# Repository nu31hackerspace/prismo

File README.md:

# Prismo – a simple NFC access controller

| Demo | PCB |
| --- | --- |
|  |  |

Prismo is an open-source NFC access controller that you can build yourself for ~500 UAH (~10 USD).
Tap a card to unlock a door or power on a machine — fully self-hosted, MIT-licensed.

<!-- HERO IMAGE — replace with a clean, well-lit photo or render of the assembled device. -->
<!--  -->

<!-- DEMO GIF — ~5s: card tap → LED turns green → relay clicks / door opens. Autoplays in GitHub. -->
<!--  -->

You can use it, for example, to:

- Open a door
- Turn on a machine
- Control whatever you want with an NFC card/key

## Features

- 🟢 **Tap-to-unlock** — present an NFC/RFID card, get instant LED + buzzer feedback and a relay action.
- 🔓 **Build it yourself for ~$10** — off-the-shelf ESP32-C3 + PN532, single-layer PCB.
- 🛠️ **DIY-friendly PCB** — single-layer, etchable at home; a great first soldering project.
- 🏠 **Self-hosted + MQTT** — integrates with Home Assistant or your own backend. No cloud lock-in.
- ⚡ **One-click flashing** — flash a pre-built firmware from your browser, no toolchain required.

## How we test our solution

Every change **Tested on real hardware** — every change runs using a physical Prismo device.
We have a test stand that allows us to verify every change and make sure everything works as expected. For more info read the [ReadMe from blackbox-e2e](/blackbox-e2e/README.md).

## What you need

| Item | Notes |
| --- | --- |
| ESP32-C3 Super Mini | The brains. ~$3. |
| PN532 NFC module | Reads the cards (powered from 3.3 V). |
| Prismo PCB + components | See the [Bill of Materials](hardware/README.md#bom-file). |
| A USB-C cable + a Chrome/Edge browser | For flashing over Web Serial. |
| 2.4 GHz WiFi | The ESP32-C3 is 2.4 GHz only. |

## Quick start

> Full build instructions live in [`hardware/README.md`](hardware/README.md) (PCB + assembly)
> and [`firmware/README.md`](firmware/README.md) (firmware).

1. **Build the board** — etch/order the [single-layer PCB](hardware/README.md), solder the
   components, and connect the PN532 and RGB LED.
2. **Flash it** — open the web flasher in Chrome and click Flash. No toolchain needed.
3. **Connect it** — the device boots, joins your 2.4 GHz WiFi, and announces itself over MQTT.
4. **Add your card** — register the card's UID in the web app; tap to unlock.

## Why are we making Prismo?

We started Prismo because we could not find a simple, low‑cost project that:

- Uses easy hardware
- Uses simple, free software
- Is friendly for beginners

Before building more features, we wrote down what we want from this project.

### General requirements

- You do not need special knowledge to build and use Prismo.
- You do not need any paid software. Everything needed is free.

### Hardware requirements

- The PCB is single‑layer, so it can be made with CNC or a simple toner‑transfer / laser–iron method.
- It should be good as a first soldering project.
- All components should be easy to solder.(We still need to define how to measure “easy to solder”.)
- You do not need special tools to solder or assemble the device.
- All parts should be off‑the‑shelf, easy to buy in common electronics shops.
- The total cost of the device should be low.

### Software requirements

- It should be easy to connect Prismo to other systems (for example, a home automation system or a custom app).
- Users should be able to move away from Prismo to another solution without problems.
- The project should use a common programming language that:
- Many developers already know
- Is easy to understand
- Works well with AI tools

## Project structure

The repository is a monorepo. That means all components of the project live in one place.

- `firmware/` – the software that runs on the Prismo device. This folder has its own README.md.
- `hardware/` – the hardware design files, such as KiCad schematics and PCB layout. This folder has its own README.md.
- `backend/` – the API + realtime sync server used to manage devices and register cards. This app is containerized and can be run locally or on a remote machine.
- `client/` – the single-page web app (served as static files) used to manage devices, register cards, and flash the board with firmware.
- `shared/` – TypeScript types shared between `backend/` and `client/`.
- `mqtt-contract/` – the shared MQTT message contract between the firmware and the backend.
- `blackbox-e2e/` – hardware-in-the-loop tests that run against a physical device on a test rig.

## Run it locally

Clone a repo

```bash
git clone https://github.com/nu31hackerspace/prismo.git
cd prismo
```

Use you favorite agent to start the dev environment, using `.agents/skills/prismo-dev-setup`

The skill will setup a few domains:

- `app.prismo.local.nu31.space`
- `mqtt.prismo.local.nu31.space`
- `postgres-viewer.prismo.local.nu31.space`

Over `mqtt.prismo.local.nu31.space` in your browser and accept the security permision

## Design system

The UI components in `client/src/components/ui` are synced to Claude Design: [Prismo Design System](https://claude.ai/design/p/379d545b-be93-4bb9-a126-a196f9bd313b). The local sync config lives in `.design-sync/` and is not committed.

## Project CI

The project uses GitHub Actions for CI. Every change is built, linted, and — for the firmware — tested on **real ESP32-C3 hardware** running on a Raspberry Pi rig before it lands on `main`. The CI also builds the firmware `*.bin` that the web flasher serves.

## License

Prismo is released under the [MIT License](LICENSE).

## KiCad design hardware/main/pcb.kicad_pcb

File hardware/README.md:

# Hardware

KiCad PCB design, STEP 3D models, and 3MF enclosure files for the Prismo NFC reader.

## Contents

- `kikad/` — KiCad project files (schematic + PCB layout)
- `body/` — 3D-printable enclosure files (3MF)
- `relay/` — Relay module design
- `*.step` — 3D assembly models for the ESP32-C3 Super Mini, PN532 NFC module, LED PCB, and full assembly

## BOM file

[Prismo BOM](https://docs.google.com/spreadsheets/d/12qys1HxDHsoDdR1gj1rnD1MEdx9XqdHl3aNJ3M6xwPU/edit?usp=sharing)

## 3d models and printed parts

All parts, model in OnShape. You can export all geometry in prefer format (SLT, STEP, ...).

[Link to OnShape project](https://cad.onshape.com/documents/9ae3614c203d1c98be9965f1/w/a32dcbcd16349b1911a14bed/e/3677841647a1055dd73aa894?renderMode=0&uiState=6a2e7c1e45387cb9ce12cedf)

The step file of PCB with PN532 cloud be download directly from github file: led_pcb.step

## Printer settings

For print the main box, use 100% infill and PETG or PLA filament.
For print the light pannel use the 20% infill and transparent PETG or PLA filament.

__The transparent filament needed only for cool light effect, the 3d printed part didn't affect the device.__

## Notes

- Hardware design changes generally do not affect firmware or web — they are independent.
- When referencing pin assignments, the source of truth is `firmware/src/config.py` (the `PIN_*` constants).

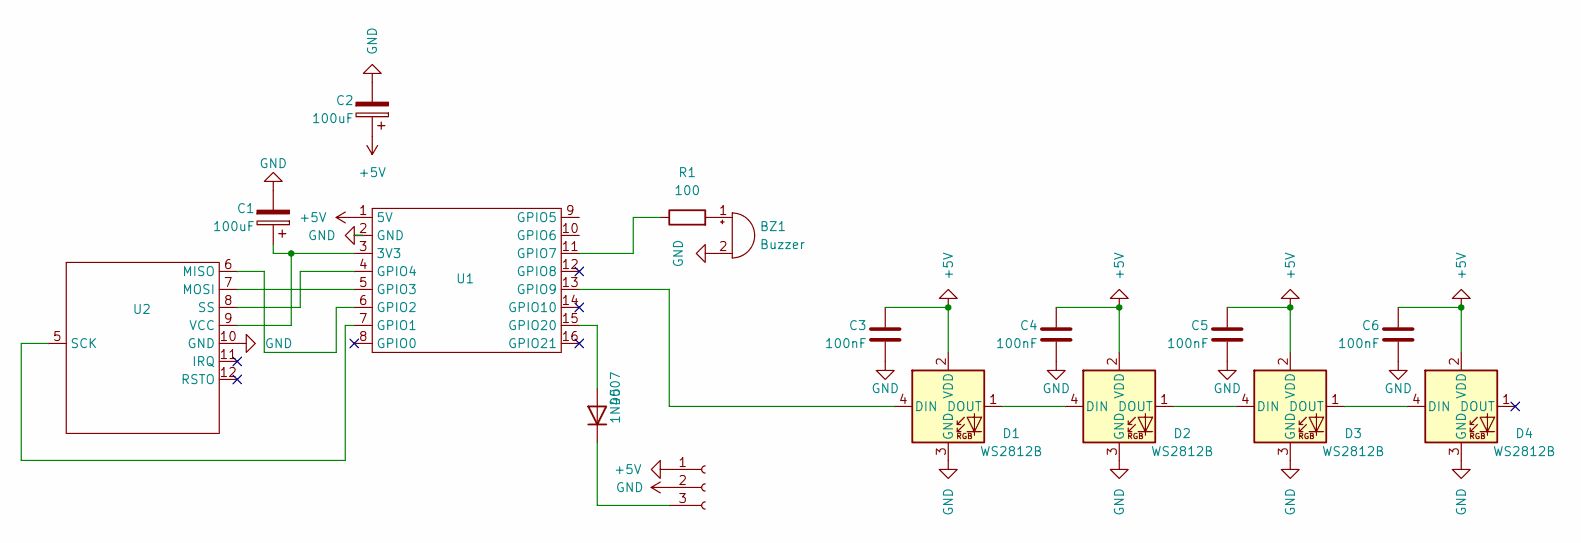
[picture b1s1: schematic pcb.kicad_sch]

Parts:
BZ1: Buzzer; MagneticBuzzer_ProSignal_ABI-010-RC
C1, C2: 100uF; CP_Radial_D5.0mm_P2.00mm
C3, C4, C5, C6: 100nF; C_Disc_D3.0mm_W1.6mm_P2.50mm
D1, D2, D3, D4: WS2812B; LED_D5.0mm-2812-D-diagonal
D5: 1N4007; D_DO-41_SOD81_P7.62mm_Horizontal
J3: Conn_01x03_Socket; JST_1x03_P2.54mm_Vertical
R1: 100; R_Axial_DIN0204_L3.6mm_D1.6mm_P7.62mm_Horizontal
U1: esp_32_c3_supper_mini
U2: PN532 NFC RFID simple (one row)

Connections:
+5V: C2.1, C3.1, C4.1, C5.1, C6.1, D1.2 (VDD), D2.2 (VDD), D3.2 (VDD), D4.2 (VDD), J3.1, U1.1 (5V)
GND: BZ1.2 (-), C1.2, C2.2, C3.2, C4.2, C5.2, C6.2, D1.3 (GND), D2.3 (GND), D3.3 (GND), D4.3 (GND), J3.2, U1.2 (GND), U2.10 (GND)
unnamed: BZ1.1 (+), R1.2
unnamed: D1.4 (DIN), U1.13 (GPIO9/SCL)
unnamed: D1.1 (DOUT), D2.4 (DIN)
unnamed: D2.1 (DOUT), D3.4 (DIN)
unnamed: D3.1 (DOUT), D4.4 (DIN)
unnamed: D5.2 (A), U1.15 (GPIO20)
unnamed: D5.1 (K), J3.3
unnamed: C1.1, U1.3 (3V3), U2.9 (VCC)
unnamed: U1.7 (GPIO1), U2.5 (SCK)
unnamed: U1.6 (GPIO2), U2.6 (MISO)
unnamed: U1.5 (GPIO3), U2.7 (MOSI)
unnamed: U1.4 (GPIO4/SCK), U2.8 (SS)
unnamed: R1.1, U1.11 (GPIO7/SS)

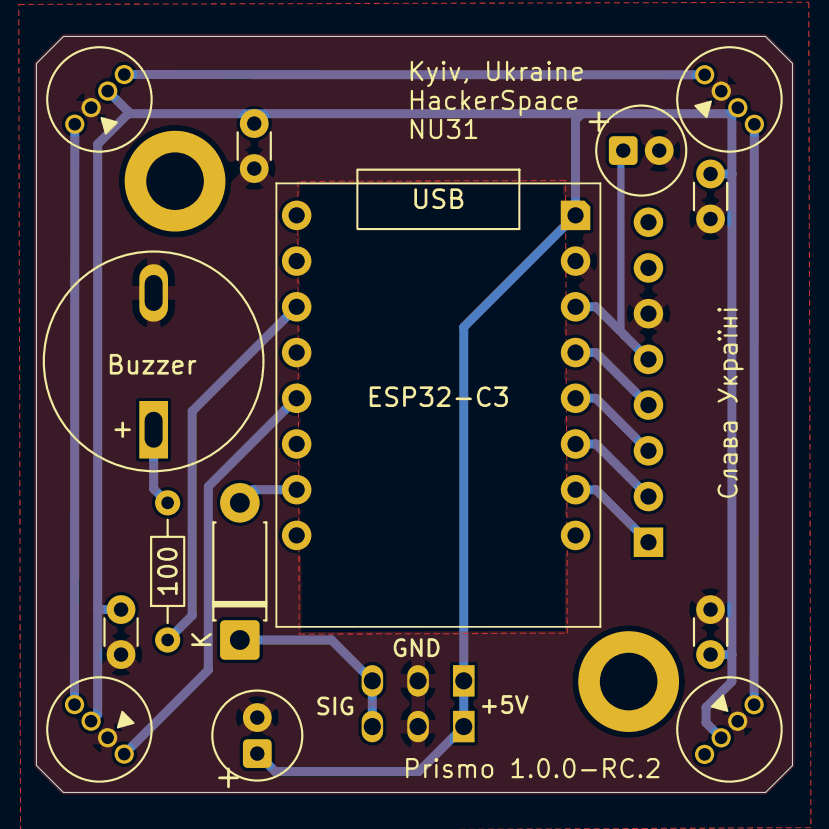
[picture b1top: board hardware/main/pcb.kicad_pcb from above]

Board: 2 copper layers, 42.0 x 42.0 mm, 16 parts (1 on the bottom side), 15 nets.

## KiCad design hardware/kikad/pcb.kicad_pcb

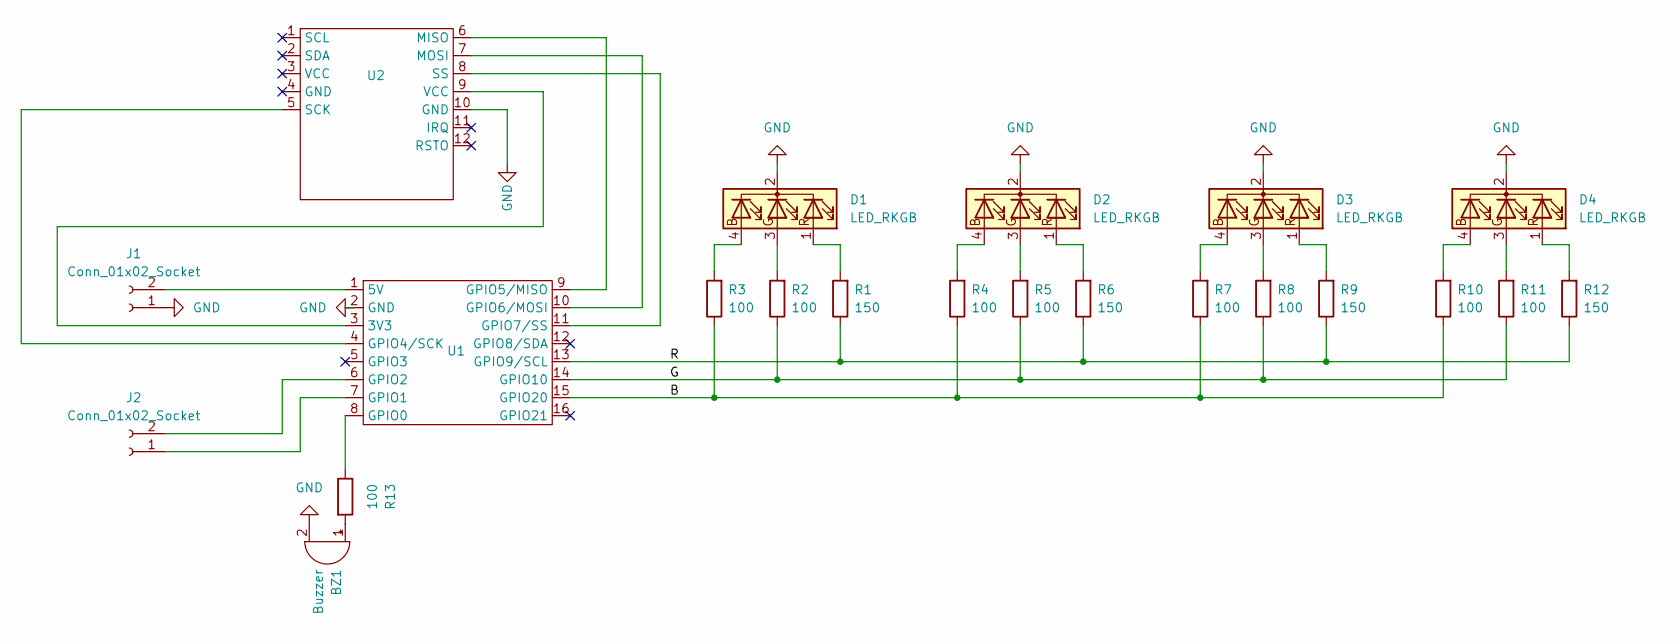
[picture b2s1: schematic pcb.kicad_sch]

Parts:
BZ1: Buzzer; MagneticBuzzer_ProSignal_ABI-010-RC
D1, D2, D3, D4: LED_RKGB; LED_D5.0mm-4_RGB_Wide_Pins_CNC_read
J1, J2: Conn_01x02_Socket; TerminalBlock_Phoenix_MKDS-1,5-2-5.08_1x02_P5.08mm_Horizont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
R1, R6, R9, R12: 150; CNC_Ready_R_Axial_DIN0204_L3.6mm_D1.6mm_P7.62mm_Horizontal
R2, R3, R4, R5, R7, R8, R10, R11, R13: 100; CNC_Ready_R_Axial_DIN0204_L3.6mm_D1.6mm_P7.62mm_Horizontal
U1: esp_32_c3_supper_mini_tht_smd
U2: PN532 NFC RFID simple (one row)

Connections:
/B: R3.1, R4.1, R7.1, R10.1, U1.15 (GPIO20)
/G: R2.1, R5.1, R8.1, R11.1, U1.14 (GPIO10)
/R: R1.1, R6.1, R9.1, R12.1, U1.13 (GPIO9/SCL)
GND: BZ1.2 (-), D1.2 (K), D2.2 (K), D3.2 (K), D4.2 (K), J1.1, U1.2 (GND), U2.10 (GND)
unnamed: BZ1.1 (+), R13.2
unnamed: D1.4 (BA), R3.2
unnamed: D1.3 (GA), R2.2
unnamed: D1.1 (RA), R1.2
unnamed: D2.4 (BA), R4.2
unnamed: D2.3 (GA), R5.2
unnamed: D2.1 (RA), R6.2
unnamed: D3.4 (BA), R7.2
unnamed: D3.3 (GA), R8.2
unnamed: D3.1 (RA), R9.2
unnamed: D4.4 (BA), R10.2
unnamed: D4.3 (GA), R11.2
unnamed: D4.1 (RA), R12.2
unnamed: J1.2, U1.1 (5V)
unnamed: J2.1, U1.7 (GPIO1)
unnamed: J2.2, U1.6 (GPIO2)
unnamed: U1.3 (3V3), U2.9 (VCC)
unnamed: R13.1, U1.8 (GPIO0)
unnamed: U1.4 (GPIO4/SCK), U2.5 (SCK)
unnamed: U1.9 (GPIO5/MISO), U2.6 (MISO)
unnamed: U1.10 (GPIO6/MOSI), U2.7 (MOSI)
unnamed: U1.11 (GPIO7/SS), U2.8 (SS)

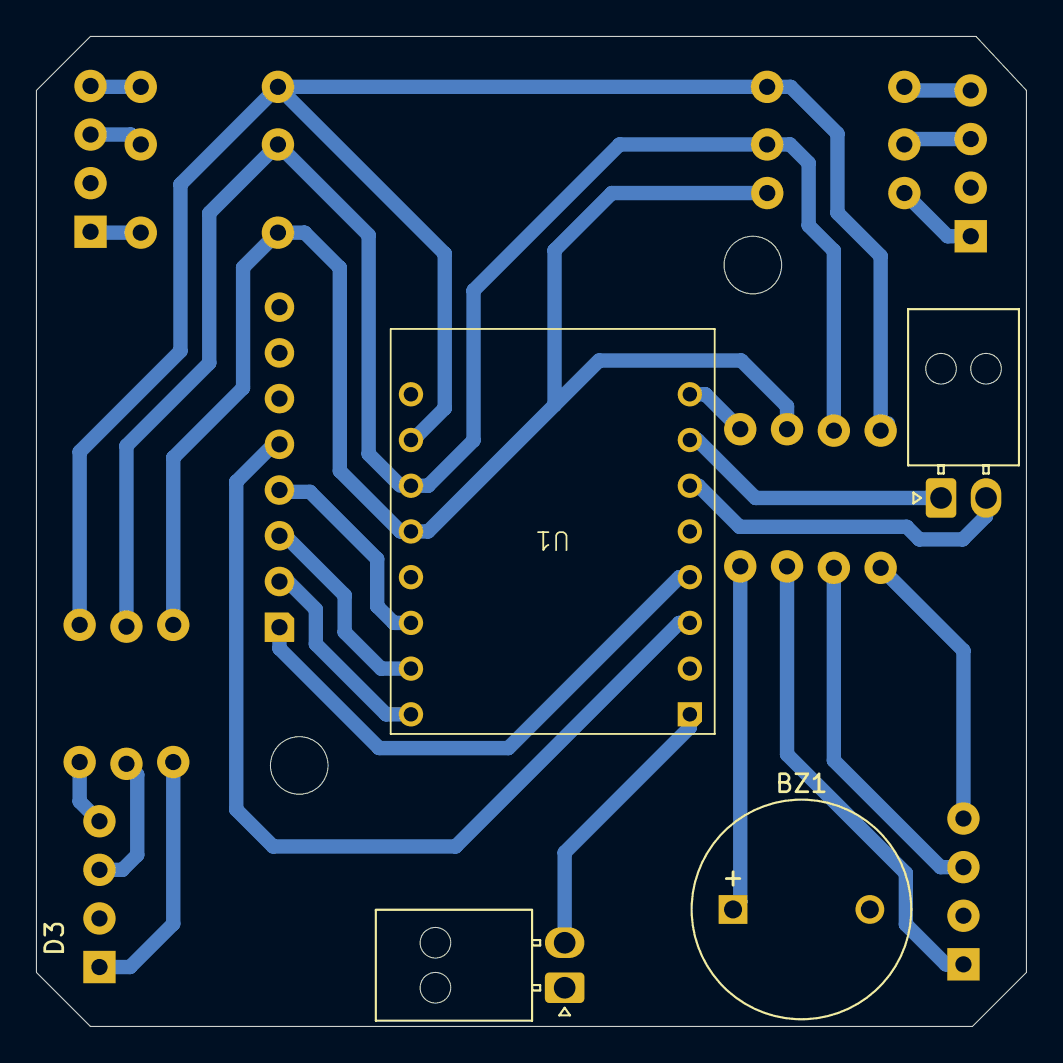
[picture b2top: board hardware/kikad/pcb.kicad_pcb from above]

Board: 2 copper layers, 55.0 x 55.0 mm, 22 parts (0 on the bottom side), 26 nets.

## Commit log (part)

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2026-02-22 remove unused files
2026-02-24 ad power for 5v esp
2026-02-25 remove the machine access code
2026-02-25 add hostname as parametrs
2026-02-25 add password to admin and update the readme for firmware
2026-02-25 add helps command
2026-02-25 make the html and css, store into files
2026-02-25 update frozen script
2026-02-25 implement step by step configuration
2026-02-26 update the success notes
2026-02-26 add read me
2026-02-26 add need files for public
2026-02-26 revert the quick start
2026-02-26 Add the web flasher
2026-02-26 add deploy
2026-02-26 fix the deploy
2026-02-26 fix the path to stack
2026-03-01 update the envvar refs
2026-03-08 add 3d printed file
2026-03-12 update 3d printed and hardware
2026-03-12 update config
2026-03-12 update flasher
2026-03-12 add flasher
2026-03-12 add qr code
2026-03-12 finish flasher
2026-03-12 update the web part
2026-03-12 update docker stack
2026-03-12 try fix
2026-03-21 use mac adress to create the prismo host and wifi
2026-03-21 remove the claude settings
2026-03-21 add logs
2026-03-21 add db to deploy
2026-03-21 add dizzle for deploy
2026-03-21 add health endpoint
2026-03-21 fix web docker build
2026-03-21 update the ci
2026-03-21 update dockre file
2026-03-21 revert the ci
2026-03-21 add cache
2026-03-21 update the ci cd
2026-03-21 fix the drizzle run
2026-03-21 update timing
2026-03-21 fix deploy
2026-03-21 make deploy simple
2026-03-21 add health check
2026-03-21 fix health check
2026-03-21 update health check
2026-03-21 change to 127.0.0.1
2026-03-21 clean health check
2026-03-21 add curl healthcheck
2026-03-22 add google auth
2026-03-22 update the google auth
2026-03-22 fix origin
2026-03-22 update drizzel
2026-03-22 fix the database
2026-03-22 fix the google id references
2026-03-23 remove the auth
2026-03-26 add logs and fix wifi
2026-03-26 add the log download from web
2026-03-27 make it simple
2026-03-27 add worker that build a firmware
2026-03-27 update the readme
2026-03-27 update timer
2026-03-28 add devices slug
2026-04-04 use mqtt for prismo device
2026-04-04 add new creds generation
2026-04-07 update firmware to mqtt robust
2026-04-07 new board, bottom layer, cut all corvers
2026-04-07 google auth
2026-04-07 update the google logic flow
2026-04-07 make the hardware folder clean
2026-04-07 fix after remove the ws function
2026-04-07 remove the drizzle migration
2026-04-10 add test to firmware, and update the web to mongo
2026-04-10 rewrite the mqtt communication from micro pyton side
2026-04-10 implement mqtt communication and update the admin pannel
2026-04-10 revert turn off buzzer
2026-04-19 migrate the mqtt from separate values for connection into mqtt_url
2026-04-19 fix the docker image build
2026-04-19 update image names
2026-04-19 fix the network
2026-04-19 fix the attached network
2026-04-19 fix the mongo url and add curl to docker image
2026-04-19 fix google secret
2026-04-19 update the device UI
2026-04-21 add bom file
2026-04-23 add tests
2026-04-25 implement the mqtt online status
2026-04-28 add debug and implement key hashes
2026-05-02 add new box 3mf and update the public mqtt url
2026-05-02 udpate the env vars for worker
2026-05-03 update the PCB and test stand project folder
2026-05-03 add ci
2026-05-03 try to fix ci
2026-05-03 fix the UI that shows the hashed value
2026-05-03 update ci
2026-05-03 update the e2e test for web job name
2026-05-03 test
2026-05-04 update kikad files
2026-05-04 add gitignore for kikad project
2026-05-05 Add mathine mode
2026-05-06 add mathine mode to device
2026-05-06 update the .gitignore and the CI /CD
2026-05-06 fix linter issue
2026-05-07 add test for mathine mode
2026-05-07 add one more test for mathine mode
2026-05-07 add linter to firmware project
2026-05-07 add rename the pipeline jobs
2026-05-07 add runner for firmware
2026-05-07 update the ci file namse
2026-05-07 Makes run test on pr for any changes
2026-05-07 Set ubuntu 24.04 for all ci job
2026-05-08 add test that test real pin output
2026-05-09 add test that verify is relay open the pin, real check by raspberry pi
2026-05-09 fix python lint issue
2026-05-09 update the tests scripts and CI
2026-05-09 fix linter
2026-05-09 add error handing for check the gpio in pi
2026-05-10 update the run test scripts
2026-05-12 add ability to build the firmware into docker
2026-05-12 add build docker image for mr check
2026-05-12 new end2end
2026-05-12 fix linter and add the download firmware test
2026-05-13 update the build cli and start ap
2026-05-14 add dev container for web part of the application that allow developer to start develop a new feature as soon as posible
2026-05-14 linter fixes
2026-05-14 remove consistency group for self hosted runner
2026-05-14 add trasistors to for led diode board
2026-05-15 update the pcb design
2026-05-15 update the board
2026-05-15 update config pin out
2026-05-16 PCB preview for PR #18 @ 056f4ff14ffb1a4c680783f59032eaf5a46d7772
2026-05-16 PCB preview for PR #18 @ 96f0b8d20dd943976f48416863753bd224822de7
2026-05-17 add gerber file
2026-05-17 PCB preview for PR #18 @ 11393c11a65ca49b29724ab4731dce98b10523e2
2026-05-17 implement key owners
2026-05-17 add test for key auth
2026-05-17 remove big core file
2026-05-17 update an UI
2026-05-17 update the user interface for web part
2026-05-17 fix linter issues
2026-05-18 Match keys page style to devices, drop /profile, tighten device online status
    - Keys page now uses the same section wrapper, grid background pattern, and
    max-w-6xl width as the devices page so the two listings line up on desktop
    - Remove the standalone /profile route and the now-unused UserAvatar component;
    the sidebar already exposes the user identity and a Sign out button
    - Drop the user link from the sidebar since /profile is gone
    - Tighten the device online detection: only update lastSeenAt when the MQTT
2026-05-21 Drop payload check in handleHeartbeat
    The status topic only ever carries an online heartbeat, so parsing and
    validating the payload was redundant — touch lastSeenAt on every status
    message and let the 10s client-side timer drive offline transitions.
2026-05-26 PCB preview for PR #18 @ 5f3d75676ef66f2a4a7ca9ac46b69ae65f9399ec
2026-05-28 PCB preview for PR #18 @ a2850dfa3015a3ccd489a1f428caa322df103133
2026-05-28 add the mqtt contact generator
2026-05-28 fix web linter
2026-05-28 feat: migrate mqtt-contract/generate.py to typescript and update agents.md
2026-05-28 feat: move mqtt-contract to root and add CI checks
2026-05-28 fix: update Dockerfile and CI workflows to use repo root context
2026-05-28 fix the code style
2026-05-28 refactor: move docker compose and mosquitto folder to root
2026-05-29 add infra start for black box e2e
2026-06-02 add 3mf file for box
2026-06-02 PCB preview for PR #18 @ 220911c36287abce53fdcb0117d53833cea12834
2026-06-02 PCB preview for PR #18 @ 3bb4978908494ef36e07231c53d9ec2aa19e104f
2026-06-10 add some black box test
2026-06-10 fix the .gitignore
2026-06-10 add new version of black box end to end tests
2026-06-11 fix: use arm runner for test image build and disable compose build
2026-06-11 fix: run Playwright in headed mode with xvfb and disable sandbox to allow Web Serial access
2026-06-11 chore: add docker system prune to free disk space on test-stand before e2e tests
2026-06-11 fix: explicitly build mqtt service before docker compose up --no-build
2026-06-11 update timeout
2026-06-11 fix: remove sudo apt-get from workflow, requires manual install on test-stand
2026-06-11 fix: use headless mode for e2e tests to fix CDP Web Serial interception
2026-06-11 fix: teststand e2e workflow improvements
2026-06-11 chore: add debugging for web serial params
2026-06-11 test: switch hardware e2e from web serial to cli flash
2026-06-12 chore: Ignore Playwright report, trace data and test-cdp.mjs
2026-06-13 fix: use commit sha from mongo job and fix e2e test flashing
    - The web app now populates commitSha into the worker job using env.COMMIT_SHA.
    - The worker uses the commitSha from the mongo job payload instead of the local env.
    - Added erase_flash before write_flash in blackbox tests to ensure clean state.
    - Purge mpy-cross caches in build.sh to prevent using old frozen module artifacts.
2026-06-13 fix format
2026-06-13 remove unneed changes
2026-06-13 PCB preview for PR #18 @ 287cc70e20d32f8a0b648a95c0971dc66a5d19e1
2026-06-13 turn on end to end for pr1
2026-06-13 PCB preview for PR #18 @ ddfbbb6df5fcd4f9c6306cd611a906e2d619f683
2026-06-13 add led pcb
2026-06-13 PCB preview for PR #18 @ 711a89bc2a65db70f2c3659d8abe27fc439271ef
2026-06-13 add tag emular tool
2026-06-14 add tag emular tool (#29)
2026-06-15 Update read me (#30)
    * add tag emular tool
    * update readme
2026-06-16 fix the buzzer
2026-06-16 add doc, fix buzzer
2026-06-17 Fix buzzer update doc (#35)
    * add tag emular tool
    * fix the buzzer
    * add doc, fix buzzer
2026-06-18 add lables
2026-06-18 PCB preview for PR #40 @ a87ae293a45924b92d01eb1eb7fd50c75db4f0b5
2026-06-18 Add labels (#40)
    * add tag emular tool
    * fix the buzzer
    * add lables
2026-06-19 add mark for 1k resistor
2026-06-19 PCB preview for PR #41 @ 9a659d693704e8bab07b60144eef0b2110e69ab5
2026-06-20 add labels
2026-06-20 PCB preview for PR #41 @ dc195d9d2797293b1c671535b2a7111218d238c2
2026-06-21 add mark for 1k resistor (#41)
    * add mark for 1k resistor
    * add labels
2026-06-21 make the firmware more stable
2026-06-21 make the firmware stable
2026-06-21 add instruction images
2026-06-21 add images
2026-06-21 Add labels (#43)
    * add tag emular tool
    * fix the buzzer
    * add lables
    * add instruction images
    * add images
2026-06-21 add mock WDT
2026-06-21 Add soldering instructions for Prismo PCB
    Added detailed soldering instructions for the Prismo PCB, including steps for main components, light components, and buzzer installation.
2026-06-21 Add soldering instructions for Prismo PCB (#44)
    Added detailed soldering instructions for the Prismo PCB, including steps for main components, light components, and buzzer installation.
2026-06-21 Fix crash (#42)
    * make the firmware more stable
    * make the firmware stable
    * add mock WDT
2026-06-23 update pcb
2026-06-23 PCB preview for PR #45 @ 68fe32a8ecfa61697062d4c18c8ca935afea62c8
2026-06-23 PCB preview for PR #45 @ 944839d6b935972caf1a29c71ff4ecb27c725c74
2026-06-27 update the pcb
2026-06-27 PCB preview for PR #45 @ 5ed01a003e52a46ffee7087843565c5ff97cd25e
2026-06-27 Update the pcb (#45)
    * add tag emular tool
    * fix the buzzer
    * update pcb
    * update the pcb
2026-06-27 make board ready for 1.0.0-alfa1
2026-06-27 remove the error pin
2026-06-27 PCB preview for PR #46 @ 0eda1bfcb981e94abae1bd558dd5add1b667e9dc
2026-06-27 update the firmware tests
2026-06-27 PCB preview for PR #46 @ 341dc81b130b05ef551797b41f919ee77daaa1c3
2026-06-27 update git ignore
2026-06-27 PCB preview for PR #46 @ a26cae7a8968993570d587cd4f4c67d7eae6bfed
2026-06-27 Simplify device (#46)
    * add tag emular tool
    * fix the buzzer
    * make board ready for 1.0.0-alfa1
    * remove the error pin
    * update the firmware tests
    * update git ignore
2026-06-29 PCB preview for PR #47 @ 9ab9eacb2dd43b6057e9a5a2c4d833215711135f
2026-06-29 add gift
2026-06-29 Update README with preview image and PCB placement
    Added a preview image and rearranged the PCB image.
2026-06-30 Update README for clarity and grammar improvements
    Improved clarity and grammar in the README file.

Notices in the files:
README.md:
License: MIT
